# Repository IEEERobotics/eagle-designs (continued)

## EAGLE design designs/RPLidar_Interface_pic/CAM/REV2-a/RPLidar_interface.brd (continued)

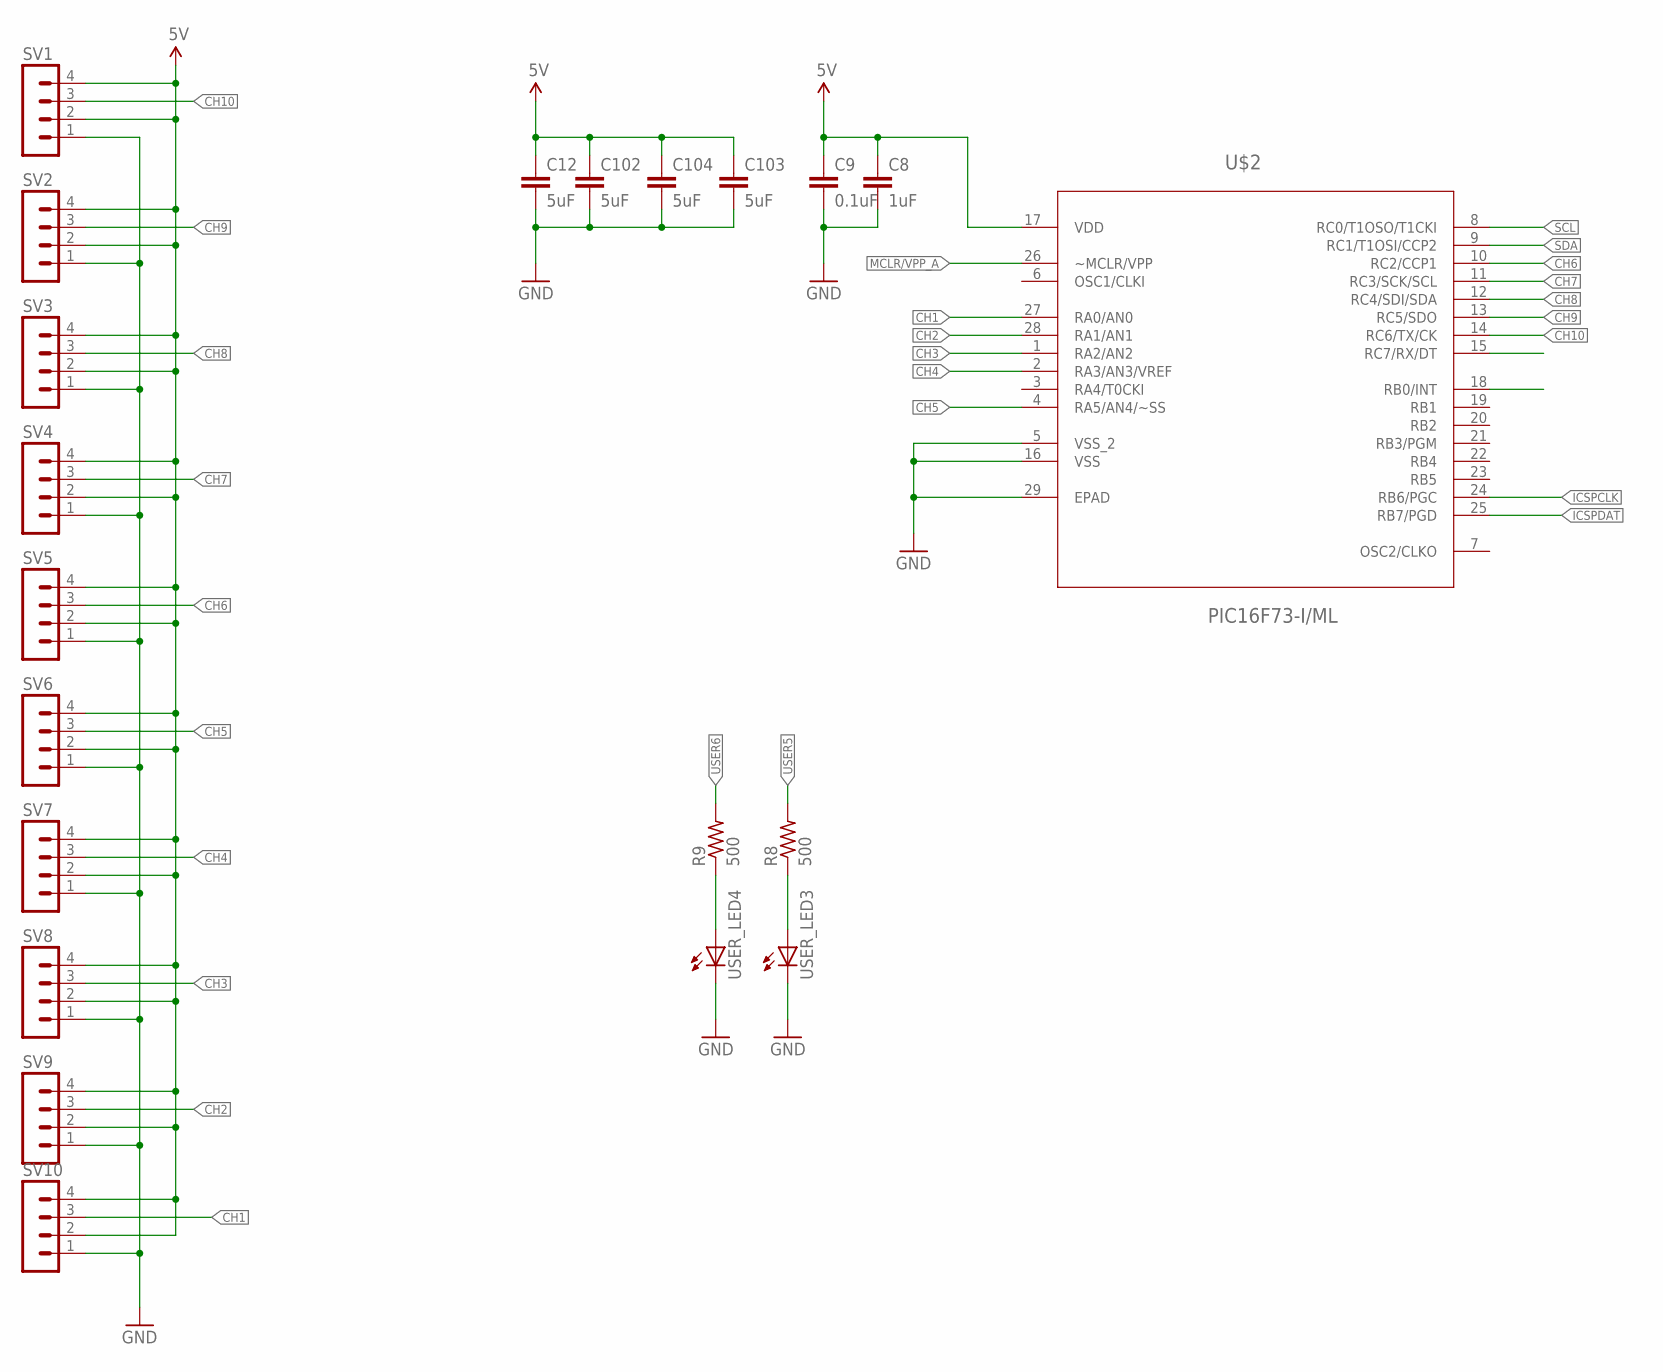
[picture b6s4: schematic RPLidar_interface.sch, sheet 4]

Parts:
C8: 1uF; C0402
C9: 0.1uF; C0402
C12, C102, C103, C104: 5uF; C0402
R8, R9: 500; R0402
SV1, SV2, SV3, SV4, SV5, SV6, SV7, SV8, SV9, SV10: MA04-1
U$2: PIC16F73-I/ML; QFN65P600X600X100-28N
USER_LED3, USER_LED4: LEDCHIP-LED0603; CHIP-LED0603

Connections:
5V: C8.1, C9.1, C12.1, C102.1, C103.1, C104.1, SV1.2, SV1.4, SV2.2, SV2.4, SV3.2, SV3.4, SV4.2, SV4.4, SV5.2, SV5.4, SV6.2, SV6.4, SV7.2, SV7.4, SV8.2, SV8.4, SV9.2, SV9.4, SV10.2, SV10.4, U$2.17 (VDD); also elsewhere on the board
CH1: SV10.3, U$2.27 (RA0/AN0)
CH2: SV9.3, U$2.28 (RA1/AN1)
CH3: SV8.3, U$2.1 (RA2/AN2)
CH4: SV7.3, U$2.2 (RA3/AN3/VREF)
CH5: SV6.3, U$2.4 (RA5/AN4/~SS)
CH6: SV5.3, U$2.10 (RC2/CCP1)
CH7: SV4.3, U$2.11 (RC3/SCK/SCL)
CH8: SV3.3, U$2.12 (RC4/SDI/SDA)
CH9: SV2.3, U$2.13 (RC5/SDO)
CH10: SV1.3, U$2.14 (RC6/TX/CK)
GND: C8.2, C9.2, C12.2, C102.2, C103.2, C104.2, SV1.1, SV2.1, SV3.1, SV4.1, SV5.1, SV6.1, SV7.1, SV8.1, SV9.1, SV10.1, U$2.5 (VSS_2), U$2.16 (VSS), U$2.29 (EPAD), USER_LED3.C, USER_LED4.C; also elsewhere on the board
ICSPCLK: U$2.24 (RB6/PGC); also elsewhere on the board
ICSPDAT: U$2.25 (RB7/PGD); also elsewhere on the board
MCLR/VPP_A: U$2.26 (~MCLR/VPP); also elsewhere on the board
unnamed: R8.1, USER_LED3.A
unnamed: R9.1, USER_LED4.A
SCL: U$2.8 (RC0/T1OSO/T1CKI); also elsewhere on the board
SDA: U$2.9 (RC1/T1OSI/CCP2); also elsewhere on the board
USER5: R8.2, U$2.15 (RC7/RX/DT)
USER6: R9.2, U$2.18 (RB0/INT)

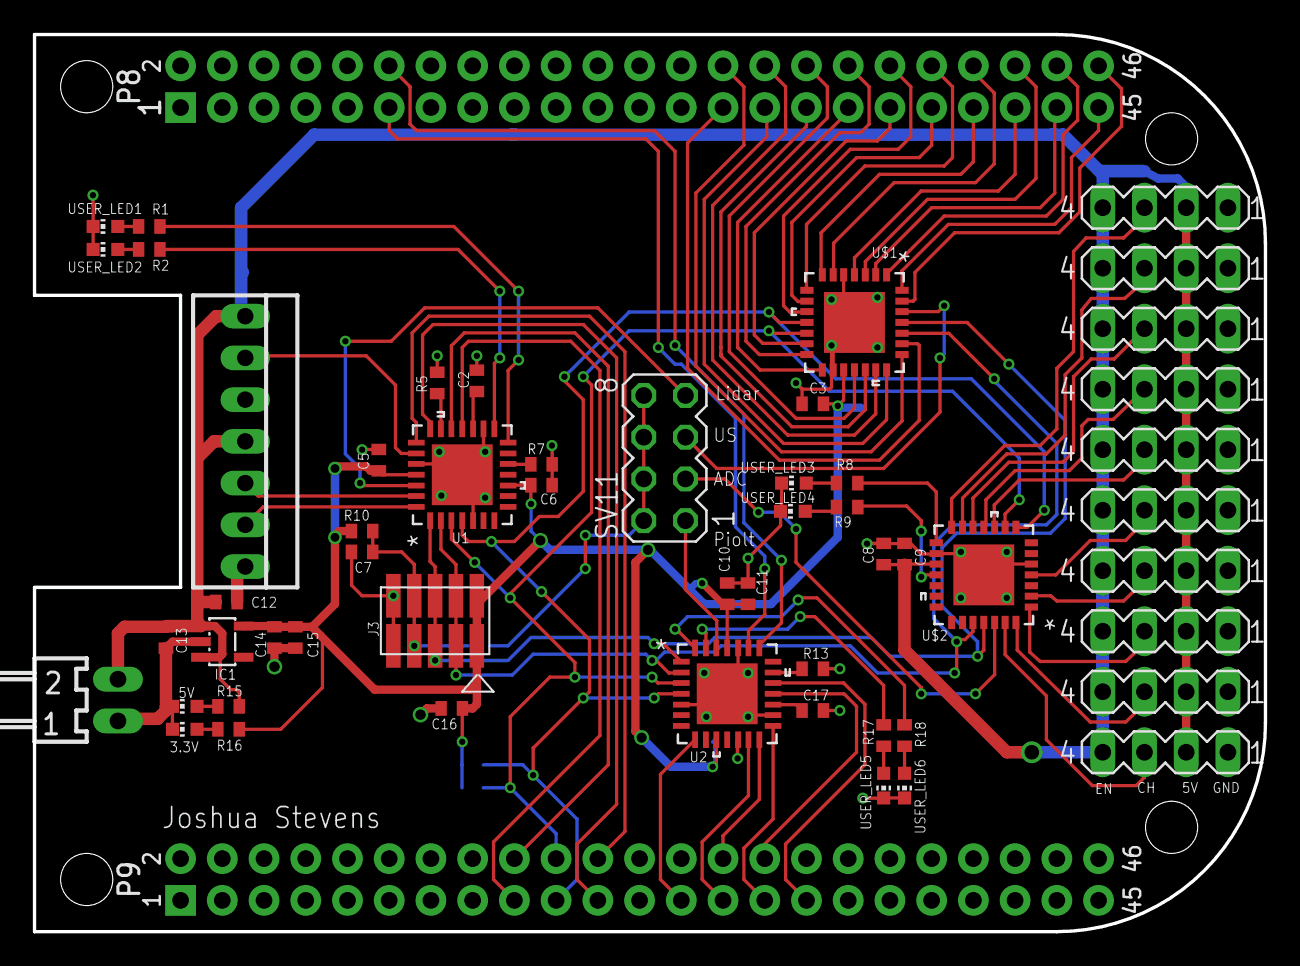
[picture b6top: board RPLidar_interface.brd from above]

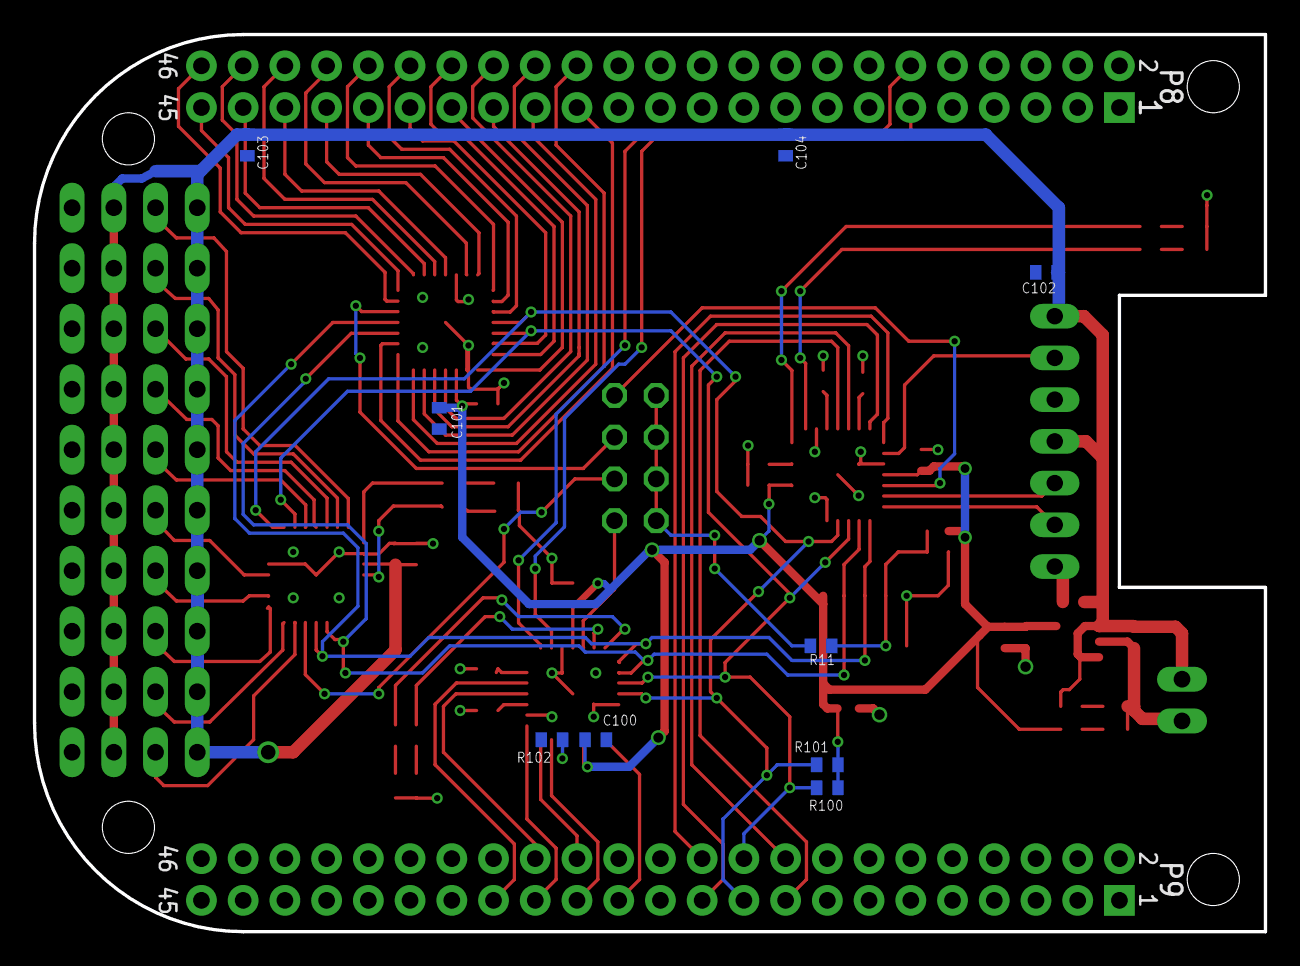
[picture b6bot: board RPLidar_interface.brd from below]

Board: 2 copper layers, 74.9 x 54.6 mm, 64 parts (9 on the bottom side), 78 nets.
